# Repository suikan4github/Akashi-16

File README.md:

# Akashi-16
Interface board to the TLV320AIC3204 EVB

# Overview
Interface schematics for the 
[EVM](https://www.ti.com/tool/TLV320AIC3204EVM-K#overview) of the 
[TLV320AIC3204](https://www.ti.com/product/TLV320AIC3204) codec. 
the interface board is based on the 
[Akashi-15](https://github.com/suikan4github/Akashi-15). 

# Design 
The EVK will be connected with this board by : 
- 20pin ribbon cable * 2 
- 10pin ribbon cable * 1

The +5V ( D&A ) and +3.3V are given from this board. The internal regulators of the TLV32AIC3204 must be enabled. 

I2C signals and 12MHz MCLCK are given from this board. The EVK is assumed to configured as I2S master. So, the BCLK and WSCLK are given from EVK. 

Nucleo F446RE connection is here : 

# Schematic

There is [PDF version](doc/Akashi-16.pdf). 

# License

This project is shared under the [MIT License](LICENSE).

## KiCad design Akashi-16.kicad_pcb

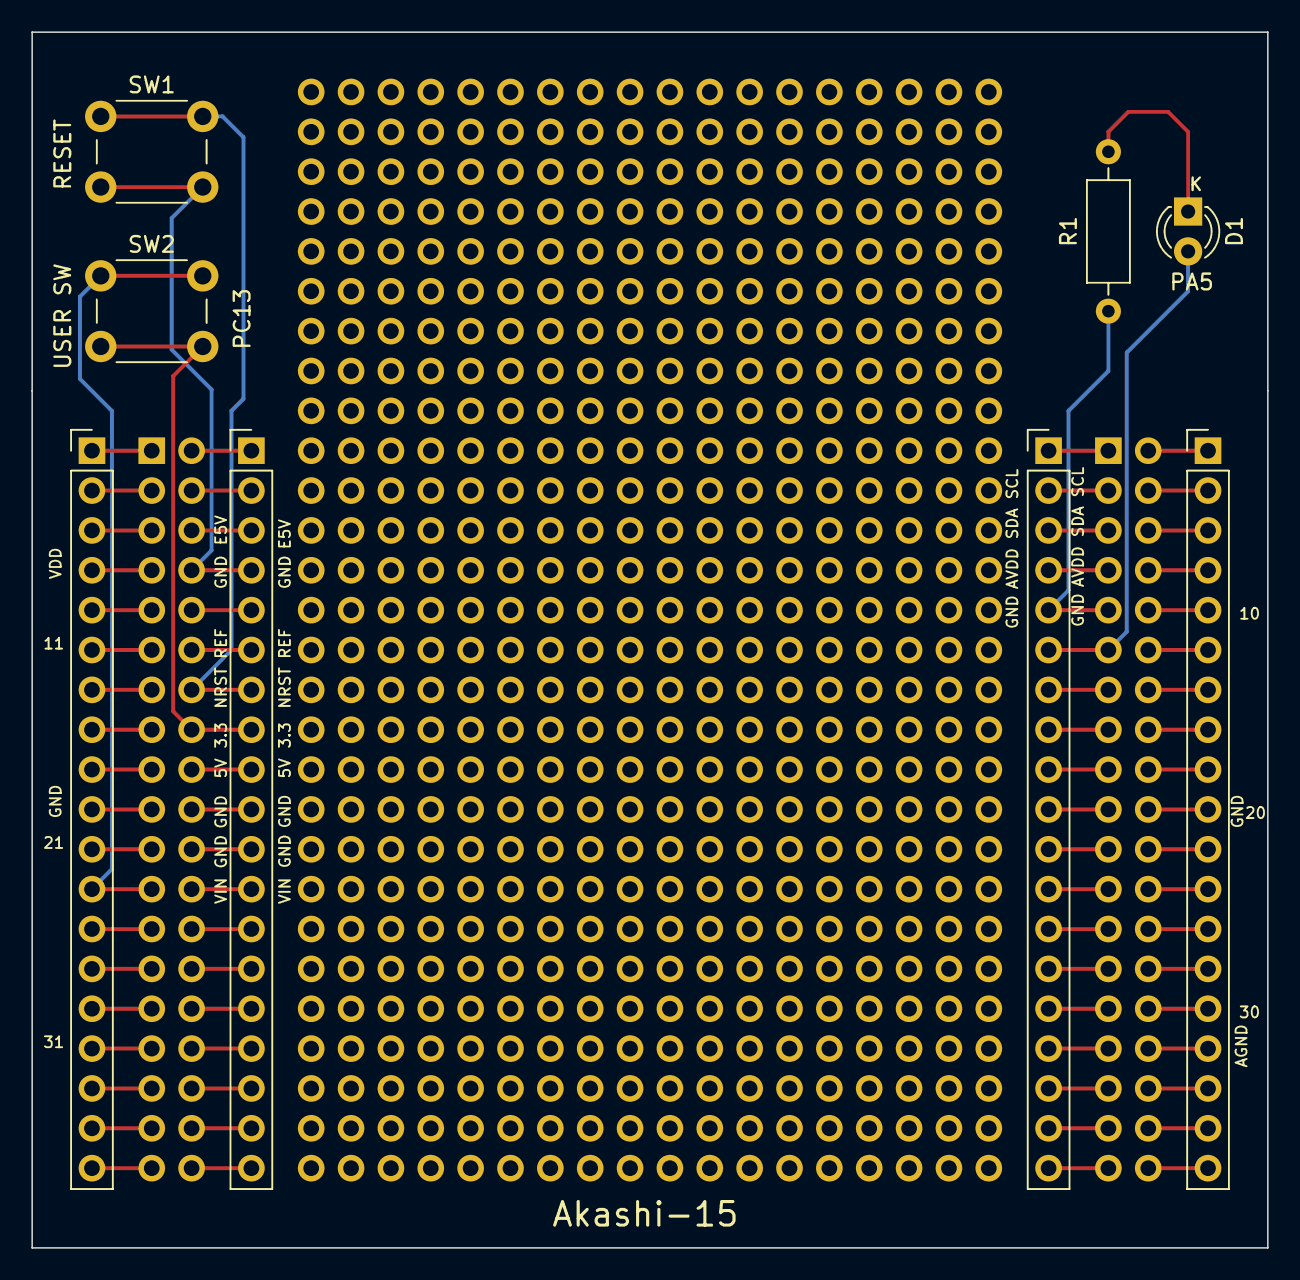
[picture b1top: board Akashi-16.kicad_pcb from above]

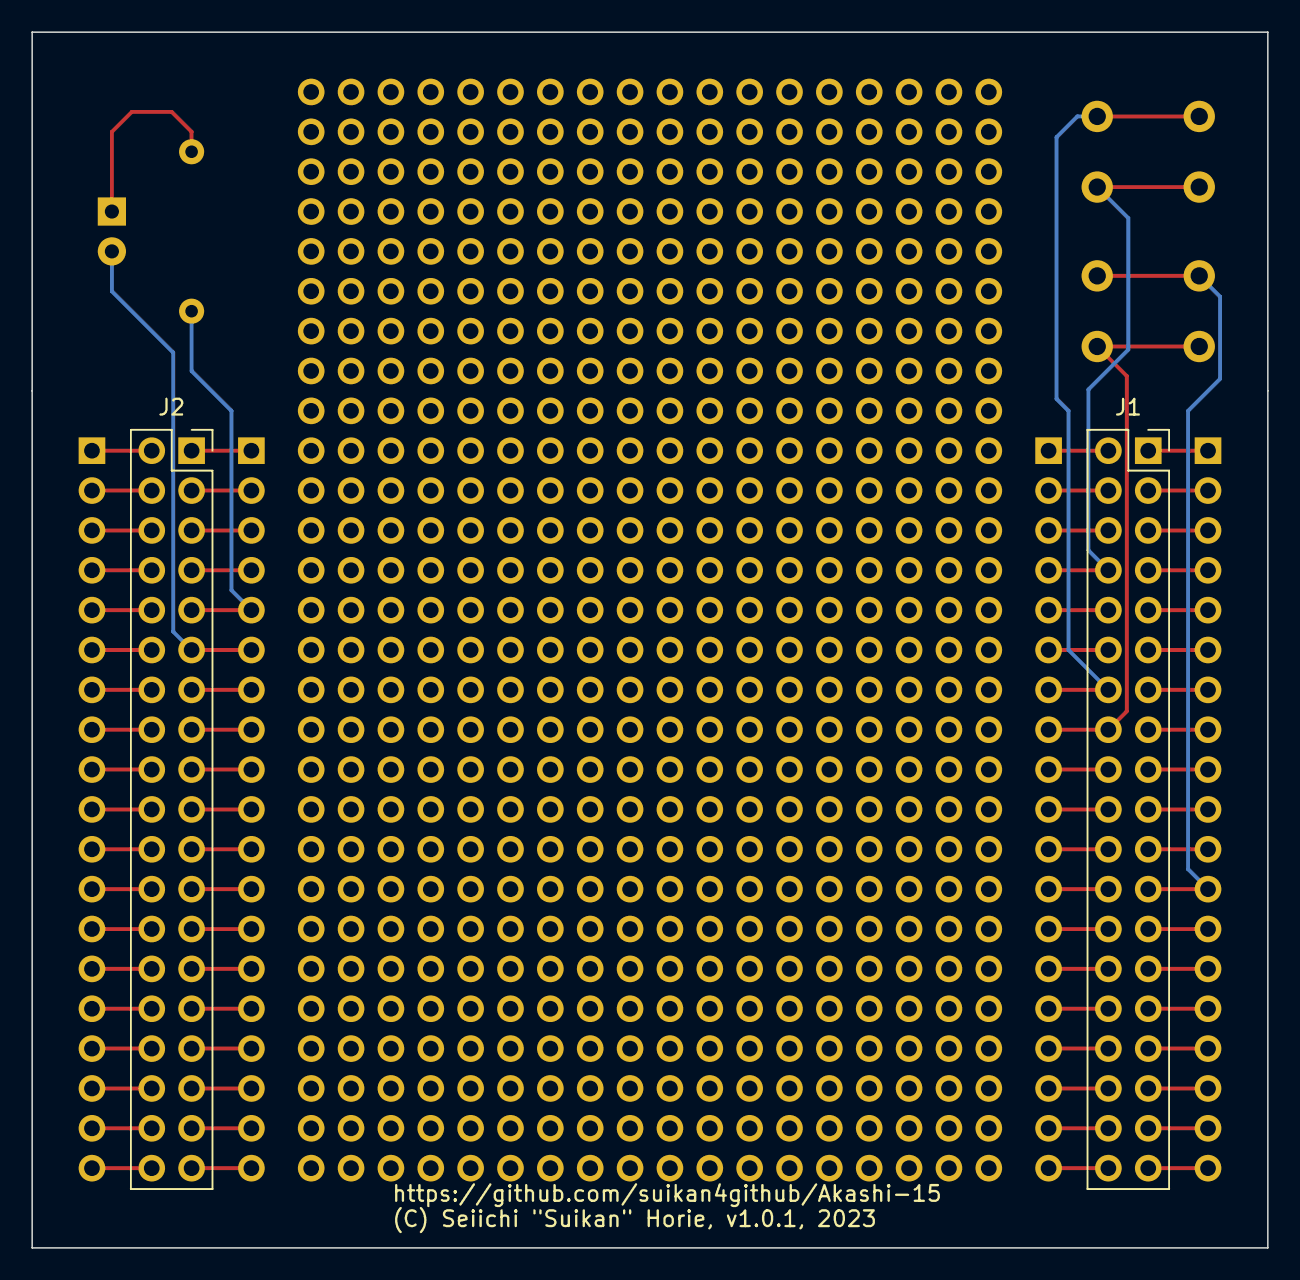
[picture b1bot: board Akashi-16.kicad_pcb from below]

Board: 2 copper layers, 78.7 x 77.5 mm, 10 parts (2 on the bottom side), 77 nets.

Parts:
D1: LED; LED_D3.0mm
J1, J2: Conn_02x19_Odd_Even; PinSocket_2x19_P2.54mm_Vertical
J3, J4, J5, J6: Conn_01x19_Pin; PinHeader_1x19_P2.54mm_Vertical
R1: 1k; R_Axial_DIN0207_L6.3mm_D2.5mm_P10.16mm_Horizontal
SW1, SW2: SW_Omron_B3FS; SW_PUSH_6mm

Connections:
GND: J1.8, J4.4, SW1.2
GND1: J2.9, J6.5, R1.2
unnamed: D1.2 (A), J2.11, J6.6
unnamed: D1.1 (K), R1.1
unnamed: J1.1, J3.1
unnamed: J1.2, J4.1
unnamed: J1.3, J3.2
unnamed: J1.4, J4.2
unnamed: J1.5, J3.3
unnamed: J1.6, J4.3
unnamed: J1.7, J3.4
unnamed: J1.9, J3.5
unnamed: J1.10, J4.5
unnamed: J1.11, J3.6
unnamed: J1.12, J4.6
unnamed: J1.13, J3.7
unnamed: J1.14, J4.7, SW1.1
unnamed: J1.15, J3.8
unnamed: J1.16, J4.8, SW2.2
unnamed: J1.17, J3.9
unnamed: J1.18, J4.9
unnamed: J1.19, J3.10
unnamed: J1.20, J4.10
unnamed: J1.21, J3.11
unnamed: J1.22, J4.11
unnamed: J1.23, J3.12, SW2.1
unnamed: J1.24, J4.12
unnamed: J1.25, J3.13
unnamed: J1.26, J4.13
unnamed: J1.27, J3.14
unnamed: J1.28, J4.14
unnamed: J1.29, J3.15
unnamed: J1.30, J4.15
unnamed: J1.31, J3.16
unnamed: J1.32, J4.16
unnamed: J1.33, J3.17
unnamed: J1.34, J4.17
unnamed: J1.35, J3.18
unnamed: J1.36, J4.18
unnamed: J1.37, J3.19
unnamed: J1.38, J4.19
unnamed: J2.1, J6.1
unnamed: J2.2, J5.1
unnamed: J2.3, J6.2
unnamed: J2.4, J5.2
unnamed: J2.5, J6.3
unnamed: J2.6, J5.3
unnamed: J2.7, J6.4
unnamed: J2.8, J5.4
unnamed: J2.10, J5.5
unnamed: J2.12, J5.6
unnamed: J2.13, J6.7
unnamed: J2.14, J5.7
unnamed: J2.15, J6.8
unnamed: J2.16, J5.8
unnamed: J2.17, J6.9
unnamed: J2.18, J5.9
unnamed: J2.19, J6.10
unnamed: J2.20, J5.10
unnamed: J2.21, J6.11
unnamed: J2.22, J5.11
unnamed: J2.23, J6.12
unnamed: J2.24, J5.12
unnamed: J2.25, J6.13
unnamed: J2.26, J5.13
unnamed: J2.27, J6.14
unnamed: J2.28, J5.14
unnamed: J2.29, J6.15
unnamed: J2.30, J5.15
unnamed: J2.31, J6.16
unnamed: J2.32, J5.16
unnamed: J2.33, J6.17
unnamed: J2.34, J5.17
unnamed: J2.35, J6.18
unnamed: J2.36, J5.18
unnamed: J2.37, J6.19
unnamed: J2.38, J5.19

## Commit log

2023-07-23 Schematics are ready.
